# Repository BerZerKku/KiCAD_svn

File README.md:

# KiCad_svn

Проект для Стихина В.Н.
Схема похожа на полумостовой преобразователь + генератор управляющих сигналов.

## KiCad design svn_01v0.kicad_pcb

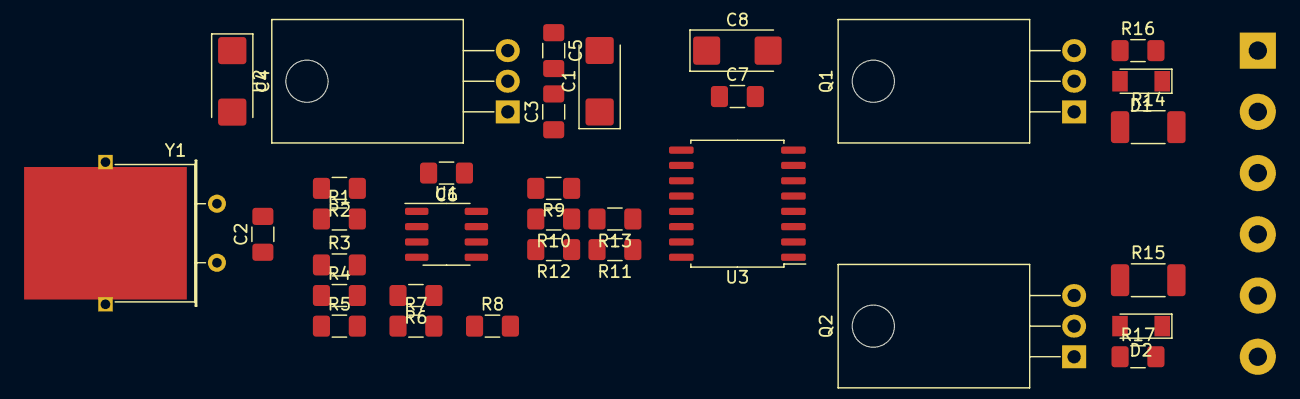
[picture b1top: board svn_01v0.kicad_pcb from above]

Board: 2 copper layers, 34 parts (1 on the bottom side), 16 nets, no tracks yet.

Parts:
C1, C4, C8: 47uF x 16V; CP_EIA-6032-28_Kemet-C_Pad2.25x2.35mm_HandSolder
C2: 100pF; C_1206_3216Metric_Pad1.42x1.75mm_HandSolder
C3, C5, C6, C7: 100nF; C_1206_3216Metric_Pad1.42x1.75mm_HandSolder
D1, D2: LL4148; D_MiniMELF
J1: Screw_Terminal_01x06; TerminalBlock_bornier-6_P5.08mm
Q1, Q2: IRF640; TO-220-3_Horizontal_TabDown
R1: 50k; R_1206_3216Metric_Pad1.42x1.75mm_HandSolder
R2, R16, R17: 1k; R_1206_3216Metric_Pad1.42x1.75mm_HandSolder
R3, R4, R5, R7, R8, R9, R10, R11, R12, R13: 10k; R_1206_3216Metric_Pad1.42x1.75mm_HandSolder
R6: ?; R_1206_3216Metric_Pad1.42x1.75mm_HandSolder
R14, R15: 10; R_2010_5025Metric_Pad1.52x2.65mm_HandSolder
U1: AD8542ARZ; SOIC-8_3.9x4.9mm_P1.27mm
U2: LM7805_TO220; TO-220-3_Horizontal_TabDown
U3: IR2110S; SOIC-16W_7.5x10.3mm_P1.27mm
Y1: 85kHz; Crystal_HC49-U_Horizontal_1EP_style2

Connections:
+5V: C4.1, C5.1, C6.1, C7.1, C8.1, R2.1, R5.1, R7.1, R13.1, U1.8, U2.3, U3.11
+12V: C1.1, C3.1, J1.1, J1.2, U2.1, U3.3, U3.7
GND: C1.2, C2.2, C3.2, C4.2, C5.2, C6.2, C7.2, C8.2, J1.5, J1.6, Q1.3, Q2.3, R4.2, R8.2, R12.2, R16.2, R17.2, U1.4, U2.2, U3.2, U3.6, U3.13, U3.15, Y1.1
unnamed: C2.1, R1.2, U1.2, Y1.2
unnamed: D1.1, R14.2, U3.8
unnamed: D1.2, Q1.1, R14.1, R16.1
unnamed: D2.1, R15.2, U3.1
unnamed: D2.2, Q2.1, R15.1, R17.1
unnamed: J1.3, Q1.2
unnamed: J1.4, Q2.2
unnamed: R1.1, R2.2, R3.1, R6.2, U1.1, U3.12
unnamed: R3.2, R4.1, R5.2, U1.3
unnamed: R6.1, R7.2, R8.1, R9.2, U1.6
unnamed: R10.1, R11.2, R12.1, R13.2
unnamed: R10.2, U1.5
unnamed: R9.1, R11.1, U1.7, U3.14

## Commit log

2020-02-06 Добавлен первый вариант схемы и замечания.
2020-02-06 Исправлена схема.
    Исправлено подключенеи ОУ.
    Разъем изменен на шести контактный.
    Добавлен преобразователь 12В в 5В.
    Добавлено несколько резисторов в обвязку ОУ.
